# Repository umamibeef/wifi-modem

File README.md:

# wifi-modem
 WiFi Modem for Vintage Computers

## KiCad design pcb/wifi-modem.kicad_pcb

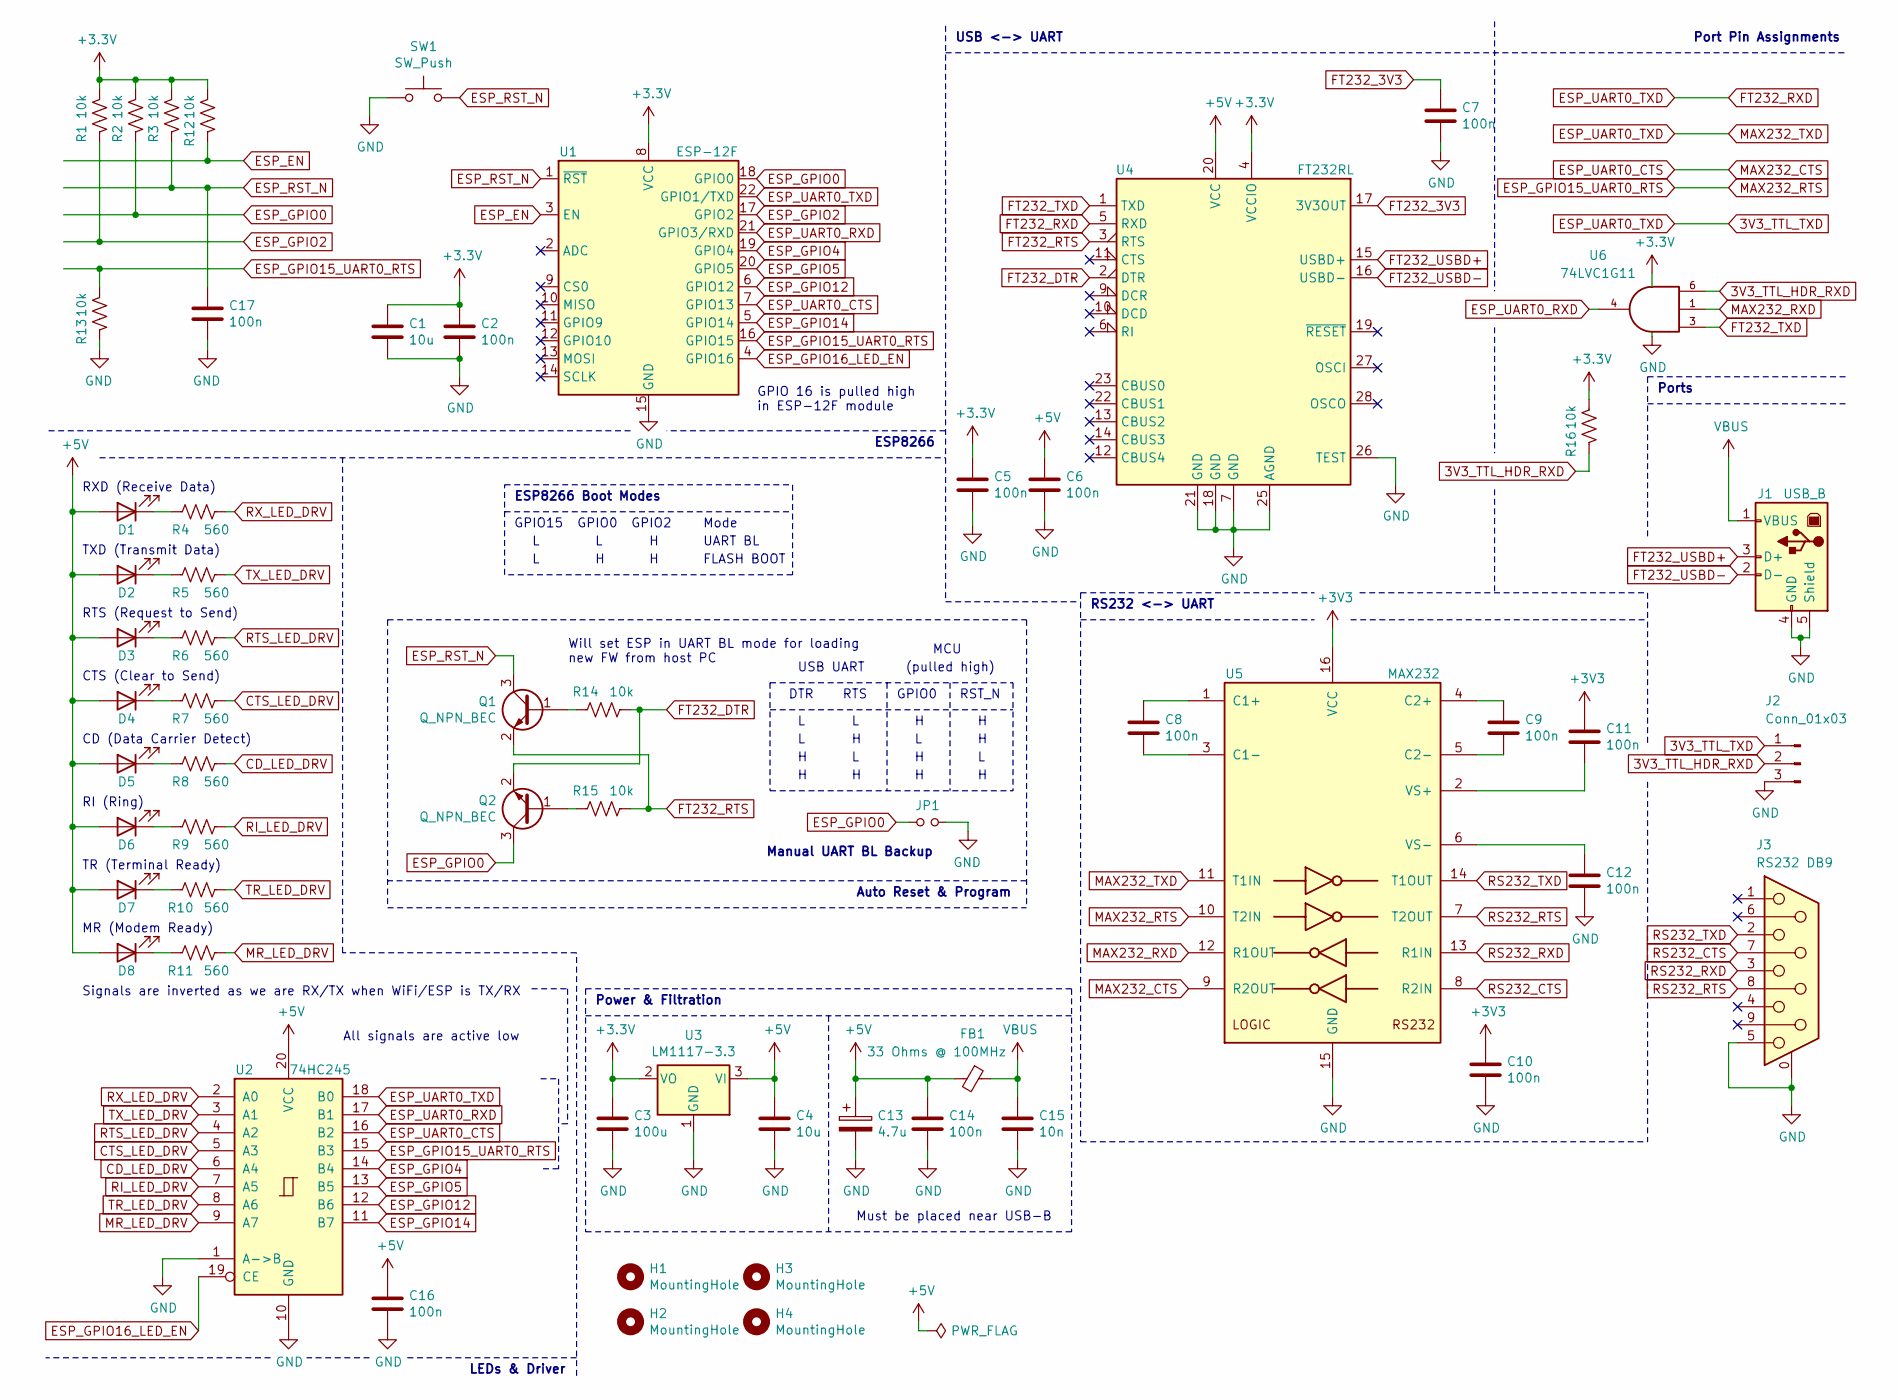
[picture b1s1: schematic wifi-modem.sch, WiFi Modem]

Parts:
C1, C4: 10u; C_0805_2012Metric_Pad1.15x1.40mm_HandSolder
C2, C5, C6, C7, C8, C9, C10, C11, C12, C14, C16, C17: 100n; C_0805_2012Metric_Pad1.15x1.40mm_HandSolder
C3: 100u; C_0805_2012Metric_Pad1.15x1.40mm_HandSolder
C13: 4.7u; CP_EIA-3216-18_Kemet-A_Pad1.58x1.35mm_HandSolder
C15: 10n; C_0805_2012Metric_Pad1.15x1.40mm_HandSolder
D1, D2, D3, D4, D5, D6, D7, D8: LED; LED_Rectangular_W3.9mm_H1.8mm_FlatTop
FB1: 33 Ohms @ 100MHz; L_0805_2012Metric_Pad1.15x1.40mm_HandSolder
H1, H2, H3, H4: MountingHole; MountingHole_3.2mm_M3
J1: USB_B; USB_B_OST_USB-B1HSxx_Horizontal
J2: Conn_01x03; PinHeader_1x03_P2.54mm_Vertical
J3: RS232 DB9; DSUB-9_Female_Horizontal_P2.77x2.84mm_EdgePinOffset9.90mm_H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
JP1: Jumper_NO_Small; PinHeader_1x02_P2.54mm_Vertical
Q1, Q2: Q_NPN_BEC; SOT-23_Handsoldering
R1, R2, R3, R12, R13, R14, R15, R16: 10k; R_0805_2012Metric_Pad1.15x1.40mm_HandSolder
R4, R5, R6, R7, R8, R9, R10, R11: 560; R_0805_2012Metric_Pad1.15x1.40mm_HandSolder
SW1: SW_Push; SW_SPST_PTS645
U1: ESP-12F; ESP-12E
U2: 74HC245; SOIC-20W_7.5x12.8mm_P1.27mm
U3: LM1117-3.3; SOT-223-3_TabPin2
U4: FT232RL; SSOP-28_5.3x10.2mm_P0.65mm
U5: MAX232; SOIC-16W_7.5x10.3mm_P1.27mm
U6: 74LVC1G11; SOT-23-6_Handsoldering

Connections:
3V3_TTL_HDR_RXD: J2.2, R16.2, U6.6
3V3_TTL_TXD: J2.1, U1.22 (GPIO1/TXD), U2.18 (B0), U4.5 (RXD), U5.11 (T1IN)
+5V: C4.1, C6.1, C13.1, C14.1, C16.1, D1.2 (A), D2.2 (A), D3.2 (A), D4.2 (A), D5.2 (A), D6.2 (A), D7.2 (A), D8.2 (A), FB1.2, U2.20 (VCC), U3.3 (VI), U4.20 (VCC)
CD_LED_DRV: R8.1, U2.6 (A4)
CTS_LED_DRV: R7.1, U2.5 (A3)
ESP_EN: R12.2, U1.3 (EN)
ESP_GPIO0: JP1.1, Q2.3 (C), R2.2, U1.18 (GPIO0)
ESP_GPIO2: R1.2, U1.17 (GPIO2)
ESP_GPIO4: U1.19 (GPIO4), U2.14 (B4)
ESP_GPIO5: U1.20 (GPIO5), U2.13 (B5)
ESP_GPIO12: U1.6 (GPIO12), U2.12 (B6)
ESP_GPIO14: U1.5 (GPIO14), U2.11 (B7)
ESP_GPIO15_UART0_RTS: R13.1, U1.16 (GPIO15), U2.15 (B3), U5.10 (T2IN)
ESP_GPIO16_LED_EN: U1.4 (GPIO16), U2.19 (CE)
ESP_RST_N: C17.1, Q1.3 (C), R3.2, SW1.2, U1.1 (~RST)
ESP_UART0_CTS: U1.7 (GPIO13), U2.16 (B2), U5.9 (R2OUT)
ESP_UART0_RXD: U1.21 (GPIO3/RXD), U2.17 (B1), U6.4
FT232_3V3: C7.1, U4.17 (3V3OUT)
FT232_DTR: Q2.2 (E), R14.2, U4.2 (DTR)
FT232_RTS: Q1.2 (E), R15.2, U4.3 (RTS)
FT232_TXD: U4.1 (TXD), U6.3
FT232_USBD+: J1.3 (D+), U4.15 (USBD+)
FT232_USBD-: J1.2 (D-), U4.16 (USBD-)
GND: C1.2, C2.2, C3.2, C4.2, C5.2, C6.2, C7.2, C10.2, C12.2, C13.2, C14.2, C15.2, C16.2, C17.2, J1.4 (GND), J1.5 (Shield), J2.3, J3.0 (PAD), J3.5, JP1.2, R13.2, SW1.1, U1.15 (GND), U2.1 (A->B), U2.10 (GND), U3.1 (GND), U4.7 (GND), U4.18 (GND), U4.21 (GND), U4.25 (AGND), U4.26 (TEST), U5.15 (GND), U6.2 (GND)
MAX232_RXD: U5.12 (R1OUT), U6.1
MR_LED_DRV: R11.1, U2.9 (A7)
unnamed: C8.1, U5.1 (C1+)
unnamed: C8.2, U5.3 (C1-)
unnamed: C9.1, U5.4 (C2+)
unnamed: C9.2, U5.5 (C2-)
unnamed: C11.2, U5.2 (VS+)
unnamed: C12.1, U5.6 (VS-)
unnamed: D1.1 (K), R4.2
unnamed: D2.1 (K), R5.2
unnamed: D3.1 (K), R6.2
unnamed: D4.1 (K), R7.2
unnamed: D5.1 (K), R8.2
unnamed: D6.1 (K), R9.2
unnamed: D7.1 (K), R10.2
unnamed: D8.1 (K), R11.2
unnamed: Q1.1 (B), R14.1
unnamed: Q2.1 (B), R15.1
RI_LED_DRV: R9.1, U2.7 (A5)
RS232_CTS: J3.7, U5.8 (R2IN)
RS232_RTS: J3.8, U5.7 (T2OUT)
RS232_RXD: J3.3, U5.13 (R1IN)
RS232_TXD: J3.2, U5.14 (T1OUT)
RTS_LED_DRV: R6.1, U2.4 (A2)
RX_LED_DRV: R4.1, U2.2 (A0)
TR_LED_DRV: R10.1, U2.8 (A6)
TX_LED_DRV: R5.1, U2.3 (A1)
VBUS: C15.1, FB1.1, J1.1 (VBUS)

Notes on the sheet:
MR (Modem Ready)
TR (Terminal Ready)
TXD (Transmit Data)
RXD (Receive Data)
RI (Ring)
CD (Data Carrier Detect)
CTS (Clear to Send)
RTS (Request to Send)
GPIO15
GPIO0
GPIO2
Mode
UART BL
FLASH BOOT
Auto Reset & Program
ESP8266 Boot Modes
RST_N
RTS
DTR
Signals are inverted as we are RX/TX when WiFi/ESP is TX/RX
All signals are active low
MCU
USB UART
Will set ESP in UART BL mode for loading new FW from host PC
(pulled high)
Power & Filtration
Must be placed near USB-B
Port Pin Assignments
Ports
ESP8266
LEDs & Driver
USB <-> UART
RS232 <-> UART
GPIO 16 is pulled high in ESP-12F module
Manual UART BL Backup

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
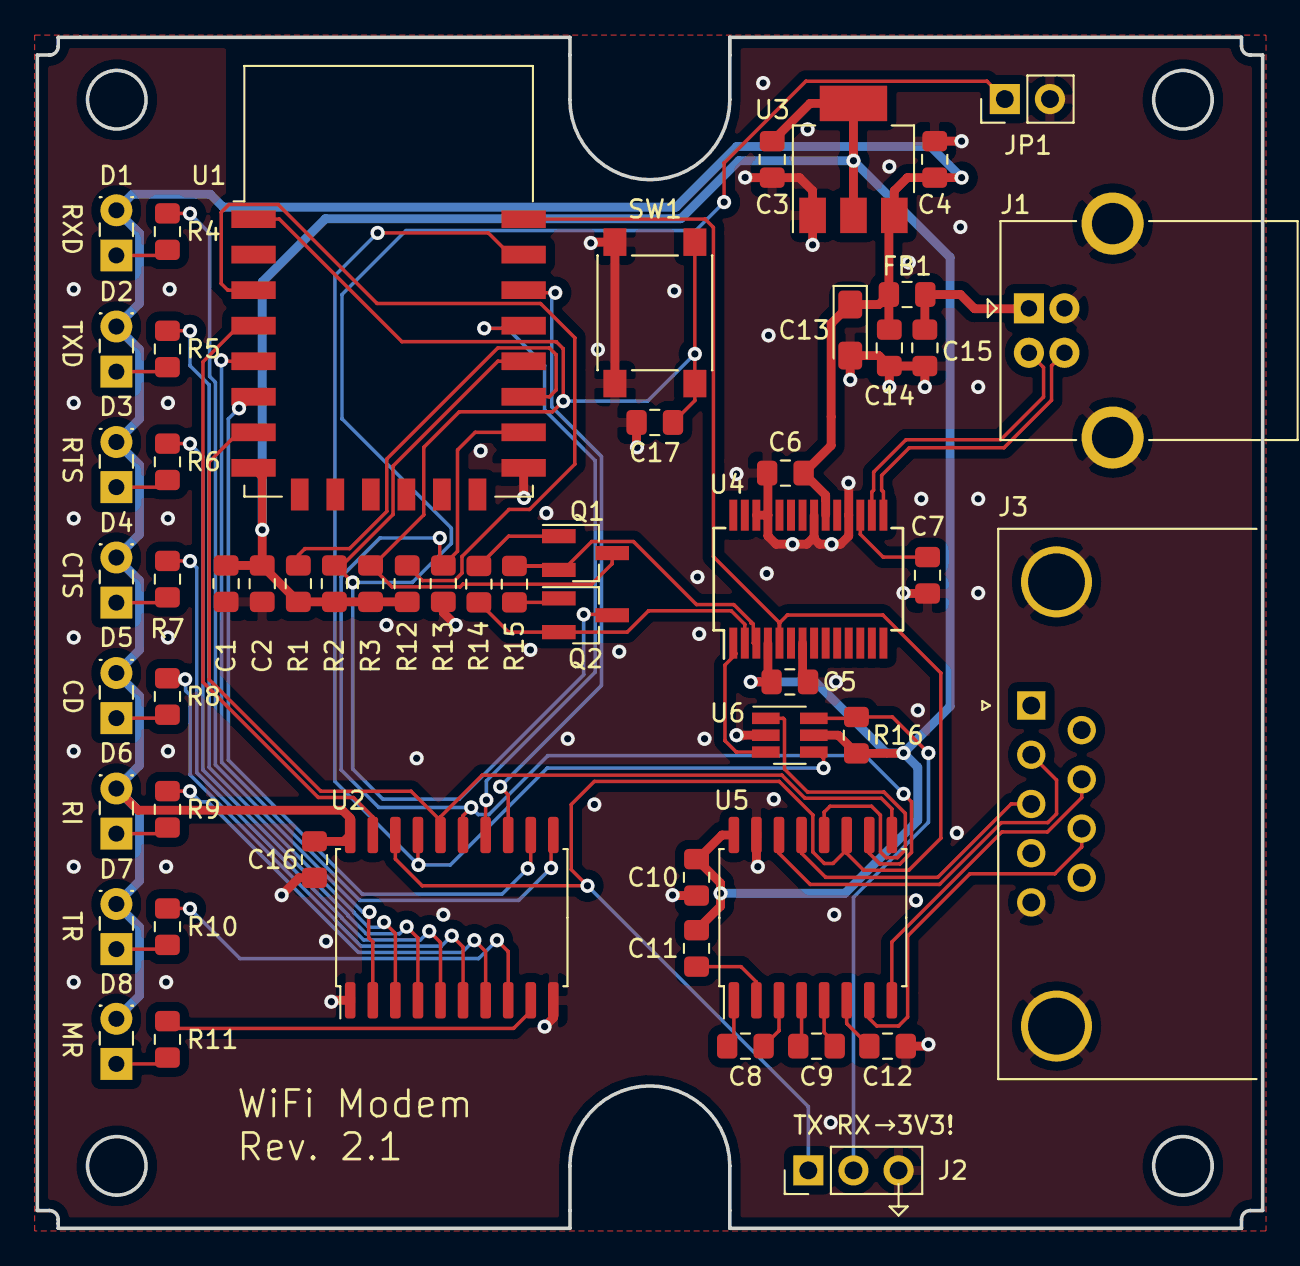
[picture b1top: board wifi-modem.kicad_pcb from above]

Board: 2 copper layers, 69.0 x 67.0 mm, 59 parts (0 on the bottom side), 53 nets.

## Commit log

2020-07-17 Rev 1.1
    * Cleaning up schematic
    * Adding missing copper void
    * Added net names for RS232 signals
2020-08-27 Initial commit of rev 2.0
    * WeMo dev board has been deconstructed into layout
    * FT232L for USB -> UART
    * USB-B port for power/debug
    * Native HW handshaking implementation
2020-08-27 Generating pdf of rev 1.1
2020-08-27 PCB layout + footprint changes
2020-08-27 Updating date and fixing swapped MAX232 pins
2020-08-27 Beautification
2020-08-31 Added 100nF cap between RST_N and GND and additional 10uF cap near 3.3V rail of ESP module
2020-08-31 Rotating VBUS filter
2020-08-31 Updating date
2020-10-28 Updating PDF of schematic
2020-10-28 Added transceiver control
2020-10-29 Updating schematic
2020-10-29 Changing VCCIO supply to external 3V3 LDO
2020-10-30 Rev 2.1 updates
    * Added 3-input AND to handle 3x serial inputs
    * Added manual UART BL mode jumper
    * Changed footprint of 2 transistors
    * Updated refdes of caps
    * Using 3V3 LDO for FT232RL IO
2020-10-31 Saving work
2020-11-01 Finished layout for 2.1
2020-11-01 Final tweaks
2020-11-01 Fixing fill
2020-11-01 Updating PDF
